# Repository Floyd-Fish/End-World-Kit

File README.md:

# End-World-Kit
末世生存装置——帮助你在废土世界中(比如核战争后的世界)更好地生存的传感器平台

## 安装的传感器

| 型号 | 描述 |
| ----- | ----------- |
| BMP280 | 温度、气压(可据此推算海拔) |
| SHT30D | 温度与湿度 |
| BH1750 | 数字光强度 |
| CCS811 | 二氧化碳与挥发性有机物 |
| MPU6050 | 6轴加速度与倾角传感器(附带温度) |
| S12SD | 紫外线强度 |
| [Open-Radiation-Detector](https://hackaday.io/project/27508-open-radiation-detector) | 辐射检测 |
| ATGM336H | 北斗+GPS双模定位模组(**未安装测试**) |

## 工程组织

原理图&PCB使用Kicad 5.1.9设计，4层板
软件使用Visual GDB+Arduino框架为ESP32开发，使用了很多第三方库

# English README

End World-Kit --- A sensor platform which makes your living more easier in the Wastland world (eg: a world after nuclear war)

## Sensors on board:

| Model | Description |
| ----- | ----------- |
| BMP280 | Temperature and Pressure (and altitude)|
| SHT30D | Temperature and Humidity |
| BH1750 | Digital Light (lux) |
| CCS811 | CO2 and TVOC |
| MPU6050 | 6-axis Gyro (and Temperature) |
| S12SD | UV Light Level |
| [Open-Radiation-Detector](https://hackaday.io/project/27508-open-radiation-detector) | Radiation Detect |
| ATGM336H | BD+GPS (**Not Tested yet**) |

## Project Structure

Schematic & PCB were designed using Kicad 5.1.9, 4-Layer PCB.

ESP32 was deved using Visual GDB & Arduino Framework, lots of 3rd-party libraries were used.

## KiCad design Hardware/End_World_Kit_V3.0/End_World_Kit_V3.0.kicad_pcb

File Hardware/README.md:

# Hardware

Developed by KiCad 5.1.9, Please Note it's not compatible with the newest KiCad Version 6.0.  

# Note

To save materials, I put 2 boards together so u need to cut them into 2 pieces.

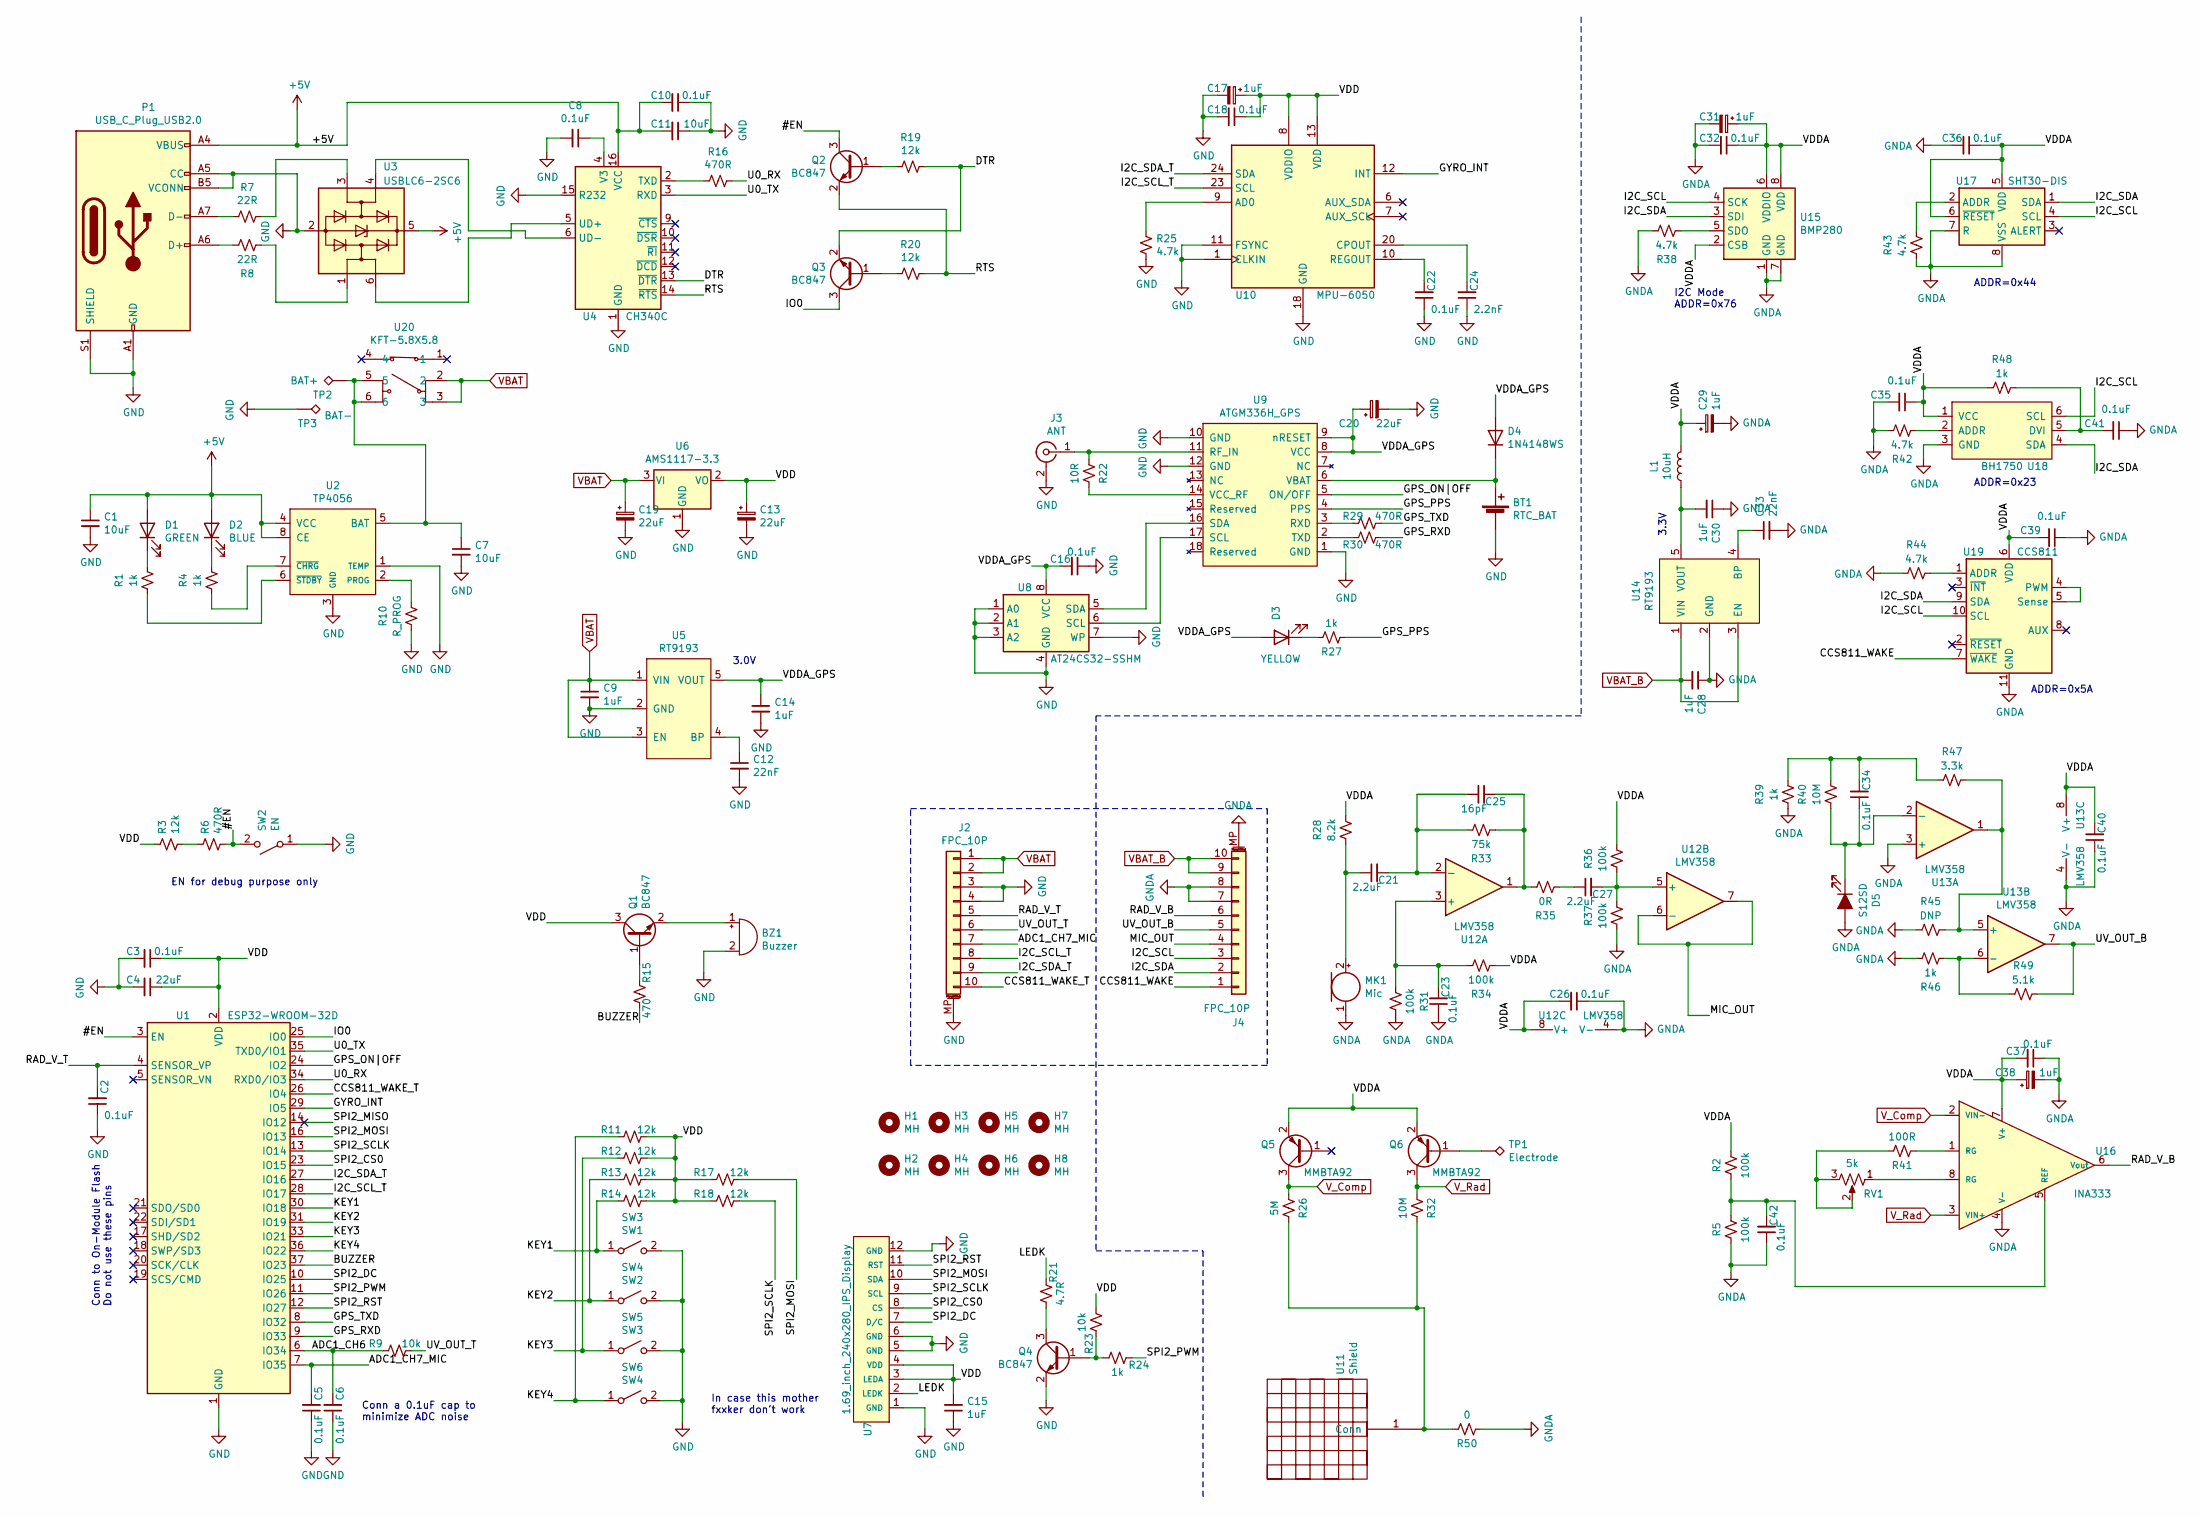
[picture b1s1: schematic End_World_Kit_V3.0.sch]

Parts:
BT1: RTC_BAT; XH414HG-IV01E
BZ1: Buzzer; 9032_BUZZER
C1, C7, C11: 10uF; C_0805_2012Metric
C2, C3, C5, C6, C8, C10, C16, C18, C22, C23, C26, C32, C34, C35, C36, C37, C39, C40, C41, C42: 0.1uF; C_0603_1608Metric
C4, C13, C19, C20: 22uF; CP_EIA-3528-15_AVX-H
C9, C14, C28, C30: 1uF; C_0805_2012Metric
C12, C33: 22nF; C_0603_1608Metric
C15: 1uF; C_0603_1608Metric
C17, C29, C31, C38: 1uF; CP_EIA-3216-12_Kemet-S
C21, C27: 2.2uF; C_0603_1608Metric
C24: 2.2nF; C_0603_1608Metric
C25: 16pF; C_0603_1608Metric
D1: GREEN; D_0805_2012Metric
D2: BLUE; D_0805_2012Metric
D3: YELLOW; D_0805_2012Metric
D4: 1N4148WS; D_SOD-323
D5: S12SD
H1, H2, H3, H4, H5, H6, H7, H8: MH; MountingHole_2.2mm_M2_Pad_Via
J2, J4: FPC_10P; TE_1-1734839-0_1x10-1MP_P0.5mm_Horizontal
J3: ANT; U.FL_Molex_MCRF_73412-0110_Vertical
L1: 10uH; L_1206_3216Metric
MK1: Mic; 4.5mmx2.2mm_Mic
P1: USB_C_Plug_USB2.0; USB_C_Receptacle_HRO_TYPE-C-31-M-12
Q1, Q2, Q3, Q4: BC847; SOT-23
Q5, Q6: MMBTA92; SOT-23
R1, R4, R24, R27, R39, R46, R48: 1k; R_0603_1608Metric
R2, R5, R31, R34, R36, R37: 100k; R_0603_1608Metric
R3, R11, R12, R13, R14, R17, R18, R19, R20: 12k; R_0603_1608Metric
R6, R16, R29, R30: 470R; R_0603_1608Metric
R7, R8: 22R; R_0603_1608Metric
R9, R23: 10k; R_0603_1608Metric
R10: R_PROG; R_0603_1608Metric
R15: 470; R_0603_1608Metric
R21: 4.7R; R_0805_2012Metric
R22: 10R; R_0603_1608Metric
R25, R38, R42, R43, R44: 4.7k; R_0603_1608Metric
R26: 5M; R_0805_2012Metric
R28: 8.2k; R_0603_1608Metric
R32: 10M; R_0805_2012Metric
R33: 75k; R_0603_1608Metric
R35: 0R; R_0603_1608Metric
R40: 10M; R_0603_1608Metric
R41: 100R; R_0603_1608Metric
R45: DNP; R_0603_1608Metric
R47: 3.3k; R_0603_1608Metric
R49: 5.1k; R_0603_1608Metric
R50: 0; R_0805_2012Metric
RV1: 5k; Potentiometer_Bourns_3214J_Horizontal
SW2: EN; turtle_little_3mmx4mm
SW3: SW1; TS-F010
SW4: SW2; TS-F010
SW5: SW3; TS-F010
SW6: SW4; TS-F010
TP1: Electrode; TestPoint_Pad_2.5x2.5mm
TP2: BAT+; TestPoint_Pad_2.5x2.5mm
TP3: BAT-; TestPoint_Pad_2.5x2.5mm
U1: ESP32-WROOM-32D; ESP32-WROOM-32
U2: TP4056; SOP-8_3.9x4.9mm_P1.27mm
U3: USBLC6-2SC6; SOT-23-6
U4: CH340C; SOIC-16_3.9x9.9mm_P1.27mm
U5, U14: RT9193; SOT-23-5
U6: AMS1117-3.3; SOT-223-3_TabPin2
U7: 1.69_inch_240x280_IPS_Display; ZJY169T-IG01
U8: AT24CS32-SSHM; SOIC-8_3.9x4.9mm_P1.27mm
U9: ATGM336H_GPS; ATGM336H-5N
U10: MPU-6050; InvenSense_QFN-24_4x4mm_P0.5mm
U11: Shield
U12, U13: LMV358; SOIC-8_3.9x4.9mm_P1.27mm
U15: BMP280; Bosch_LGA-8_2x2.5mm_P0.65mm_ClockwisePinNumbering
U16: INA333; VSSOP-8_3.0x3.0mm_P0.65mm
U17: SHT30-DIS; SHT3X
U18: BH1750
U19: CCS811; AMS_LGA-10-1EP_2.7x4mm_P0.6mm
U20: KFT-5.8X5.8; KFT-5.8x5.8

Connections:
+5V: C1.1, C10.2, C11.2, D1.2 (A), D2.2 (A), P1.A4 (VBUS), P1.A9 (VBUS), P1.B4 (VBUS), P1.B9 (VBUS), U2.4 (VCC), U2.8 (CE), U3.5 (VBUS), U4.16 (VCC)
/#EN: Q2.3 (C), R6.1, SW2.2 (B), U1.3 (EN)
/ADC1_CH6: C6.2, R9.2, U1.6 (IO34)
/ADC1_CH7_MIC: C5.2, J2.7, U1.7 (IO35)
/BUZZER: R15.1, U1.37 (IO23)
/CCS811_WAKE: J4.1, U19.7 (~WAKE)
/CCS811_WAKE_T: J2.10, U1.26 (IO4)
/DTR: Q3.2 (E), R19.1, U4.13 (~DTR)
/GPS_ON|OFF: U1.24 (IO2), U9.5 (ON/OFF)
/GPS_PPS: R27.2, U9.4 (PPS)
/GPS_RXD: R30.2, U1.9 (IO33)
/GPS_TXD: R29.2, U1.8 (IO32)
/GYRO_INT: U1.29 (IO5), U10.12 (INT)
/I2C_SCL: J4.3, U15.4 (SCK), U17.4 (SCL), U18.6 (SCL), U19.10 (SCL)
/I2C_SCL_T: J2.8, U1.28 (IO17), U10.23 (SCL)
/I2C_SDA: J4.2, U15.3 (SDI), U17.1 (SDA), U18.4 (SDA), U19.9 (SDA)
/I2C_SDA_T: J2.9, U1.27 (IO16), U10.24 (SDA)
/IO0: Q3.3 (C), U1.25 (IO0)
/KEY1: R14.2, SW3.1 (A), U1.30 (IO18)
/KEY2: R13.2, SW4.1 (A), U1.31 (IO19)
/KEY3: R12.2, SW5.1 (A), U1.33 (IO21)
/KEY4: R11.2, SW6.1 (A), U1.36 (IO22)
/LEDK: R21.2, U7.2 (LEDK)
/MIC_OUT: J4.4, U12.6 (-), U12.7
/RAD_V_B: J4.6, U16.6 (Vout)
/RAD_V_T: C2.2, J2.5, U1.4 (SENSOR_VP)
/RTS: Q2.2 (E), R20.1, U4.14 (~RTS)
/SPI2_CS0: U1.23 (IO15), U7.8 (CS)
/SPI2_DC: U1.10 (IO25), U7.7 (D/C)
/SPI2_MOSI: R17.1, U1.16 (IO13), U7.10 (SDA)
/SPI2_PWM: R24.2, U1.11 (IO26)
/SPI2_RST: U1.12 (IO27), U7.11 (RST)
/SPI2_SCLK: R18.1, U1.13 (IO14), U7.9 (SCL)
/U0_RX: R16.1, U1.34 (RXD0/IO3)
/U0_TX: U1.35 (TXD0/IO1), U4.3 (RXD)
/UV_OUT_B: J4.5, R49.1, U13.7
/UV_OUT_T: J2.6, R9.1
/VDD: C3.1, C4.1, C13.1, C15.2, C17.1, C18.1, Q1.3 (C), R3.1, R11.1, R12.1, R13.1, R14.1, R17.2, R18.2, R23.1, U1.2 (VDD), U6.2 (VO), U7.3 (LEDA), U7.4 (VDD), U10.8 (VDDIO), U10.13 (VDD)
/VDDA: C26.2, C29.1, C31.1, C32.1, C35.1, C36.1, C37.2, C38.1, C39.2, C40.2, L1.2, Q5.2 (E), Q6.2 (E), R2.2, R28.1, R34.2, R36.1, R48.2, U12.8 (V+), U13.8 (V+), U15.2 (CSB), U15.6 (VDDIO), U15.8 (VDD), U16.7 (V+), U17.5 (VDD), U17.6 (~RESET), U18.1 (VCC), U19.6 (VDD)
/VDDA_GPS: C14.1, C16.2, C20.1, D3.2 (A), D4.2 (A), U5.5 (VOUT), U8.8 (VCC), U9.8 (VCC), U9.9 (nRESET)
GND: BT1.2 (-), BZ1.2 (+), C1.2, C2.1, C3.2, C4.2, C5.1, C6.1, C7.2, C8.2, C9.2, C10.1, C11.1, C12.2, C13.2, C14.2, C15.1, C16.1, C17.2, C18.2, C19.2, C20.2, C22.1, C24.1, J2.3, J2.4, J2.MP (MountPin), J3.2 (Ext), P1.A1 (GND), P1.A5 (CC), P1.A12 (GND), P1.B1 (GND), P1.B5 (VCONN), P1.B12 (GND), P1.S1 (SHIELD), Q4.2 (E), R10.1, R25.1, SW2.1 (A), SW3.2 (B), SW4.2 (B), SW5.2 (B), SW6.2 (B), TP3.1, U1.1 (GND), U1.15 (GND), U1.38 (GND), U1.39 (GND), U2.1 (TEMP), U2.3 (GND), U3.2 (GND), U4.1 (GND), U4.15 (R232), U5.2 (GND), U6.1 (GND), U7.1 (GND), U7.5 (GND), U7.6 (GND), U7.12 (GND), U8.1 (A0), U8.2 (A1), U8.3 (A2), U8.4 (GND), U8.7 (WP), U9.1 (GND), U9.10 (GND), U9.12 (GND), U10.1 (CLKIN), U10.11 (FSYNC), U10.18 (GND)
GNDA: C23.1, C26.1, C28.1, C29.2, C30.1, C31.2, C32.2, C33.2, C35.2, C36.2, C37.1, C38.2, C39.1, C40.1, C41.1, C42.1, D5.2 (A), J4.7, J4.8, J4.MP (MountPin), MK1.1 (-), R5.1, R31.1, R37.2, R38.2, R39.1, R42.1, R43.1, R44.2, R45.2, R46.1, R50.1, U12.4 (V-), U13.3 (+), U13.4 (V-), U14.2 (GND), U15.1 (GND), U15.7 (GND), U16.4 (V-), U17.7 (R), U17.8 (VSS), U17.9 (VSS), U18.3 (GND), U19.11 (GND)
unnamed: BT1.1 (+), D4.1 (K), U9.6 (VBAT)
unnamed: BZ1.1 (-), Q1.2 (E)
unnamed: C7.1, TP2.1, U2.5 (BAT), U20.5, U20.6
unnamed: C8.1, U4.4 (V3)
unnamed: C12.1, U5.4 (BP)
unnamed: C21.1, MK1.2 (+), R28.2
unnamed: C21.2, C25.1, R33.1, U12.2 (-)
unnamed: C22.2, U10.10 (REGOUT)
unnamed: C23.2, R31.2, R34.1, U12.3 (+)
unnamed: C24.2, U10.20 (CPOUT)
unnamed: C25.2, R33.2, R35.1, U12.1
unnamed: C27.1, R35.2
unnamed: C27.2, R36.2, R37.1, U12.5 (+)
unnamed: C30.2, L1.1, U14.5 (VOUT)
unnamed: C33.1, U14.4 (BP)
unnamed: C34.1, D5.1 (K), R40.2, U13.2 (-)
unnamed: C34.2, R39.2, R40.1, R47.1
unnamed: C41.2, R48.1, U18.5 (DVI)
unnamed: C42.2, R2.1, R5.2, U16.5 (REF)
unnamed: D1.1 (K), R1.2
unnamed: D2.1 (K), R4.2
unnamed: D3.1 (K), R27.1
unnamed: J3.1 (In), R22.2, U9.11 (RF_IN)
unnamed: P1.A6 (D+), R8.2
unnamed: P1.A7 (D-), R7.2
unnamed: Q1.1 (B), R15.2
unnamed: Q2.1 (B), R19.2
unnamed: Q3.1 (B), R20.2
unnamed: Q4.1 (B), R23.2, R24.1
unnamed: Q4.3 (C), R21.1
unnamed: Q6.1 (B), TP1.1
unnamed: R1.1, U2.6 (~STDBY)
unnamed: R3.2, R6.2
unnamed: R4.1, U2.7 (~CHRG)
unnamed: R7.1, U3.3 (I/O2)
unnamed: R8.1, U3.1 (I/O1)
unnamed: R10.2, U2.2 (PROG)
unnamed: R16.2, U4.2 (TXD)
unnamed: R22.1, U9.14 (VCC_RF)
unnamed: R25.2, U10.9 (AD0)
unnamed: R26.2, R32.2, R50.2, U11.1
unnamed: R29.1, U9.3 (RXD)
unnamed: R30.1, U9.2 (TXD)
unnamed: R38.1, U15.5 (SDO)
unnamed: R41.1, U16.1 (RG)
unnamed: R41.2, RV1.2, RV1.3
unnamed: R42.2, U18.2 (ADDR)
unnamed: R43.2, U17.2 (ADDR)
unnamed: R44.1, U19.1 (ADDR)
unnamed: R45.1, R47.2, U13.1, U13.5 (+)
unnamed: R46.2, R49.2, U13.6 (-)
unnamed: RV1.1, U16.8 (RG)
unnamed: U3.4 (I/O2), U4.6 (UD-)
unnamed: U3.6 (I/O1), U4.5 (UD+)
unnamed: U8.5 (SDA), U9.16 (SDA)
unnamed: U8.6 (SCL), U9.17 (SCL)
unnamed: U19.4 (PWM), U19.5 (Sense)
VBAT: C9.1, C19.1, J2.1, J2.2, U5.1 (VIN), U5.3 (EN), U6.3 (VI), U20.2, U20.3
VBAT_B: C28.2, J4.9, J4.10, U14.1 (VIN), U14.3 (EN)
V_Comp: Q5.3 (C), R26.1, U16.2 (VIN-)
V_Rad: Q6.3 (C), R32.1, U16.3 (VIN+)

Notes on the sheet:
In case this mother fxxker don't work
Conn a 0.1uF cap to minimize ADC noise
EN for debug purpose only
Conn to On-Module Flash Do not use these pins
I2C Mode ADDR=0x76
ADDR=0x44
ADDR=0x23
ADDR=0x5A
3.0V
3.3V

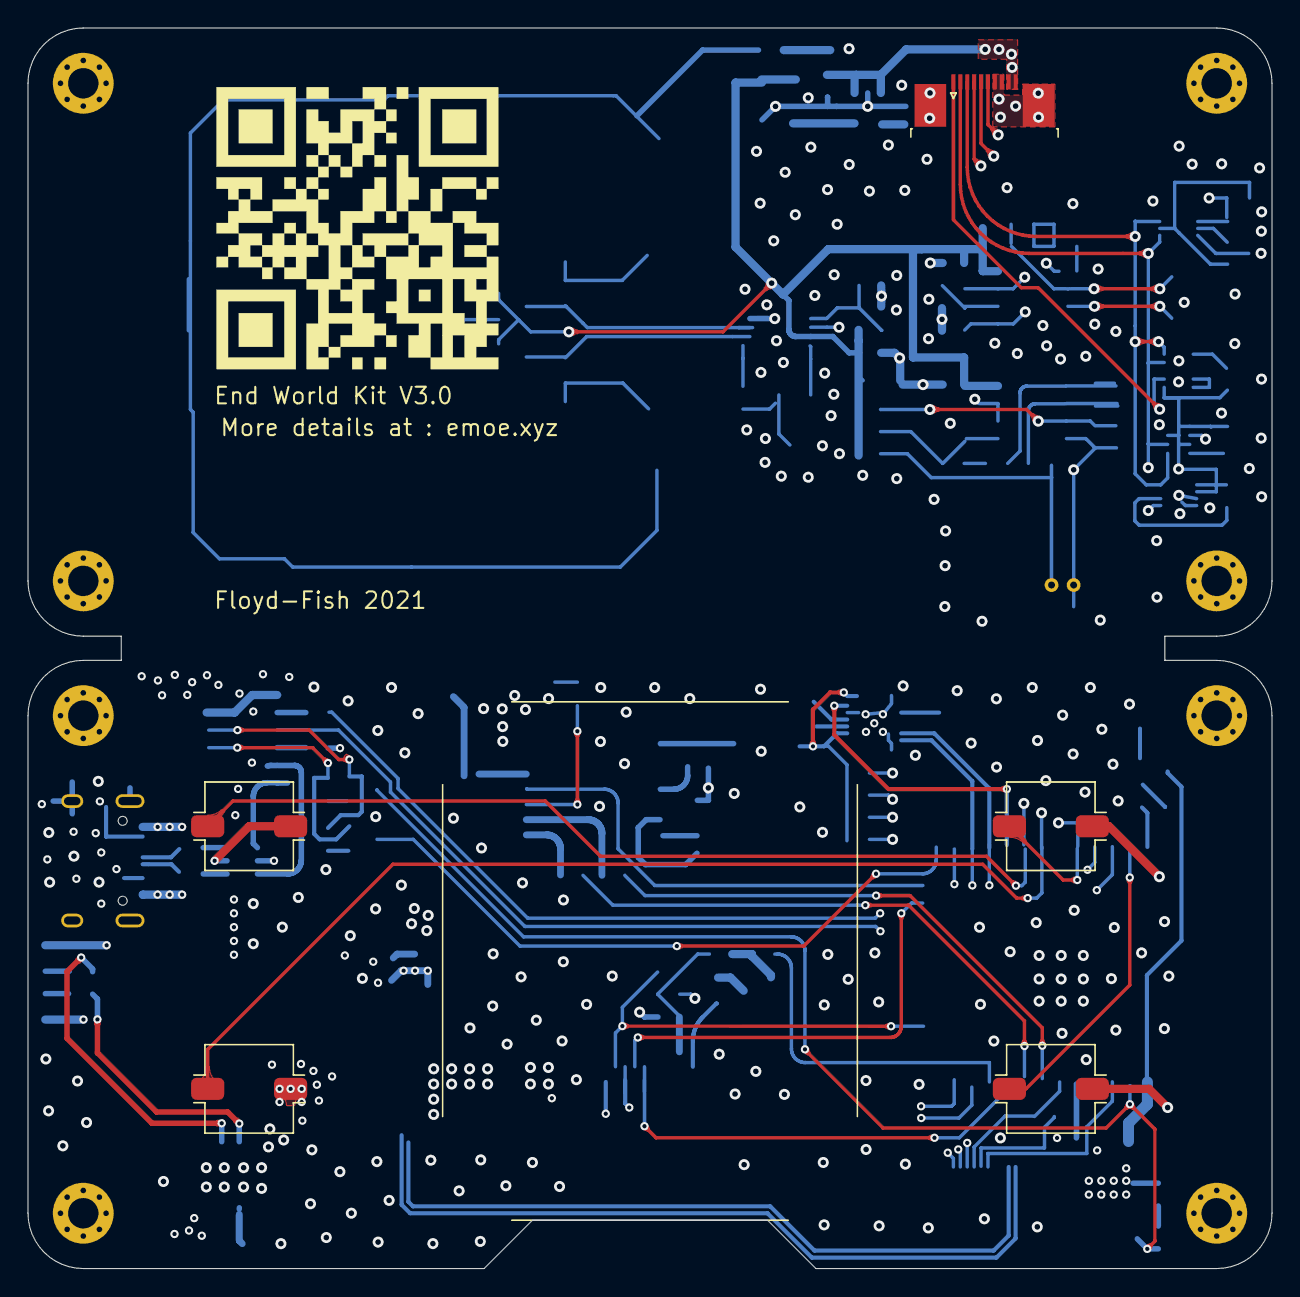
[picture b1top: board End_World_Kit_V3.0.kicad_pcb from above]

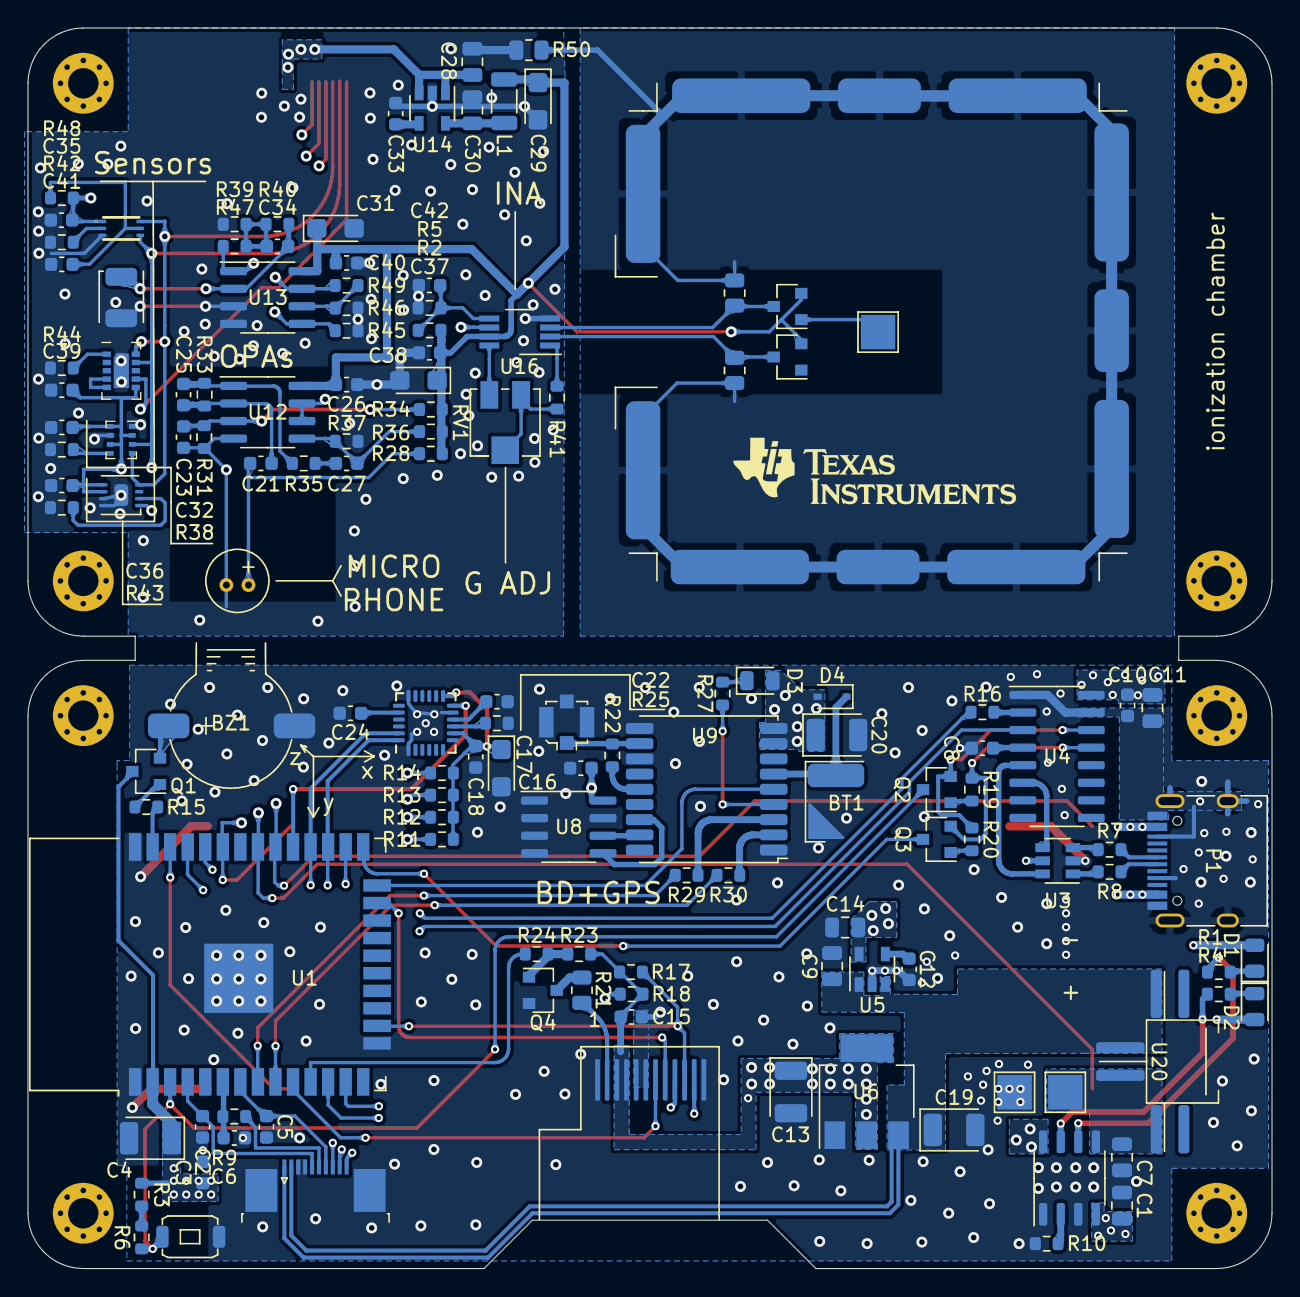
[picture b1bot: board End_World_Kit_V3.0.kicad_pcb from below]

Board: 4 copper layers, 90.0 x 89.8 mm, 148 parts (134 on the bottom side), 103 nets.

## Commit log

2021-10-18 Update PCB Designs
